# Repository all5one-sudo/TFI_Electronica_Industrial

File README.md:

# Electrónica Industrial: Trabajo Final de Integración

## Consigna

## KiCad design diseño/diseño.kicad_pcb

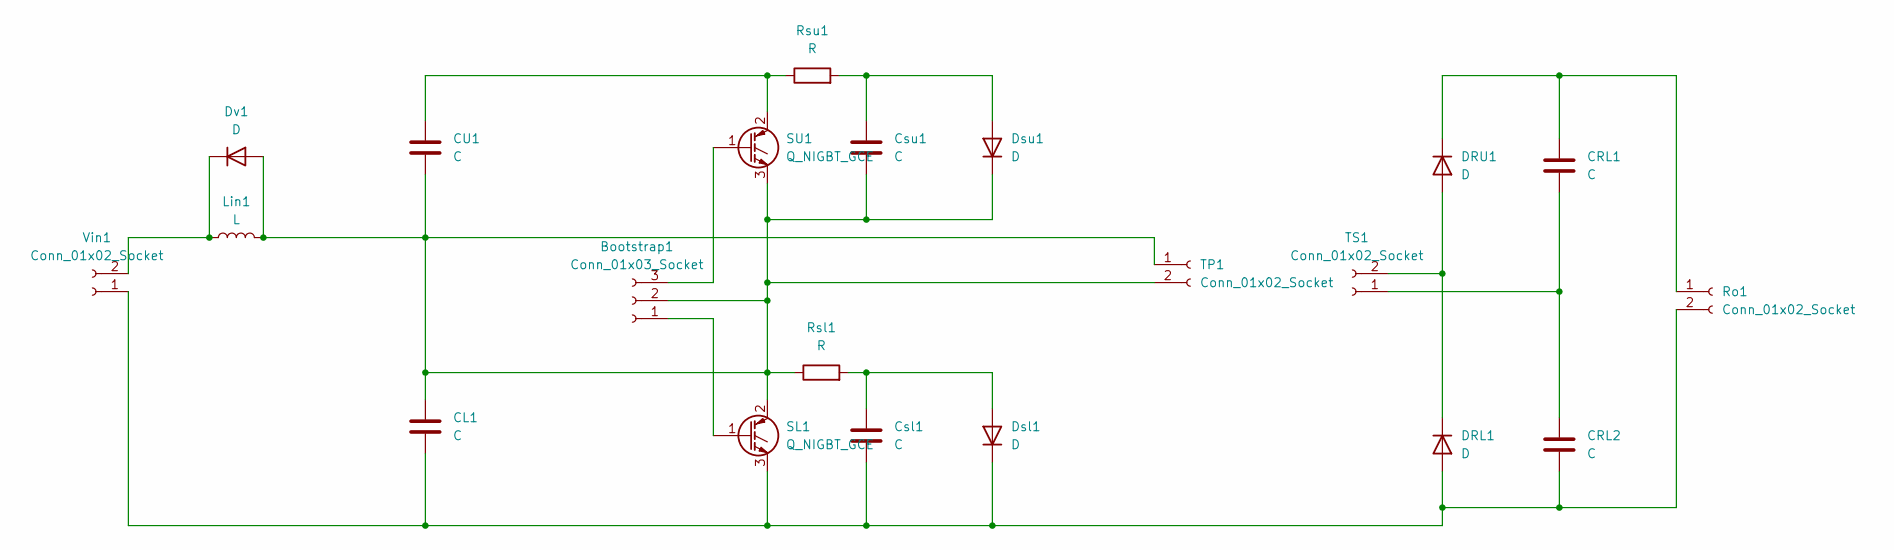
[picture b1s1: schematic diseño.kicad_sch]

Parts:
Bootstrap1: Conn_01x03_Socket; PinSocket_1x03_P2.54mm_Vertical
CL1: C; CP_Axial_L42.0mm_D35.0mm_P45.00mm_Horizontal
CRL1, CRL2: C; CP_Radial_D14.0mm_P7.50mm
CU1: C; CP_Axial_L42.0mm_D35.0mm_P45.00mm_Horizontal
Csl1: C; C_Rect_L13.0mm_W4.0mm_P10.00mm_FKS3_FKP3_MKS4
Csu1: C; C_Rect_L13.0mm_W4.0mm_P10.00mm_FKS3_FKP3_MKS4
DRL1: D; TO-220-2_Vertical
DRU1: D; TO-220-2_Vertical
Dsl1: D; D_DO-41_SOD81_P7.62mm_Horizontal
Dsu1: D; D_DO-41_SOD81_P7.62mm_Horizontal
Dv1: D; D_5KP_P10.16mm_Horizontal
Lin1: L; L_Axial_L30.0mm_D8.0mm_P7.62mm_Vertical_Fastron_77A
Ro1: Conn_01x02_Socket; PhoenixContact_MCV_1,5_2-G-5.08_1x02_P5.08mm_Vertical
Rsl1: R; R_Axial_DIN0918_L18.0mm_D9.0mm_P7.62mm_Vertical
Rsu1: R; R_Axial_DIN0918_L18.0mm_D9.0mm_P7.62mm_Vertical
SL1: Q_NIGBT_GCE; TO-264-3_Vertical
SU1: Q_NIGBT_GCE; TO-264-3_Vertical
TP1: Conn_01x02_Socket; PhoenixContact_MCV_1,5_2-G-5.08_1x02_P5.08mm_Vertical
TS1: Conn_01x02_Socket; PhoenixContact_MCV_1,5_2-G-5.08_1x02_P5.08mm_Vertical
Vin1: Conn_01x02_Socket; PhoenixContact_MCV_1,5_2-G-5.08_1x02_P5.08mm_Vertical

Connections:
unnamed: Bootstrap1.1, SL1.1 (G)
unnamed: Bootstrap1.2, CL1.1, CU1.2, Csu1.2, Dsu1.1 (K), Dv1.2 (A), Lin1.2, Rsl1.1, SL1.2 (C), SU1.3 (E), TP1.1, TP1.2
unnamed: Bootstrap1.3, SU1.1 (G)
unnamed: CL1.2, CRL2.2, Csl1.2, DRL1.2 (A), Dsl1.1 (K), Ro1.2, SL1.3 (E), Vin1.1
unnamed: DRL1.1 (K), DRU1.2 (A), TS1.2
unnamed: CRL1.1, DRU1.1 (K), Ro1.1
unnamed: Csl1.1, Dsl1.2 (A), Rsl1.2
unnamed: Csu1.1, Dsu1.2 (A), Rsu1.2
unnamed: Dv1.1 (K), Lin1.1, Vin1.2
unnamed: CU1.1, Rsu1.1, SU1.2 (C)
unnamed: CRL1.2, CRL2.1, TS1.1

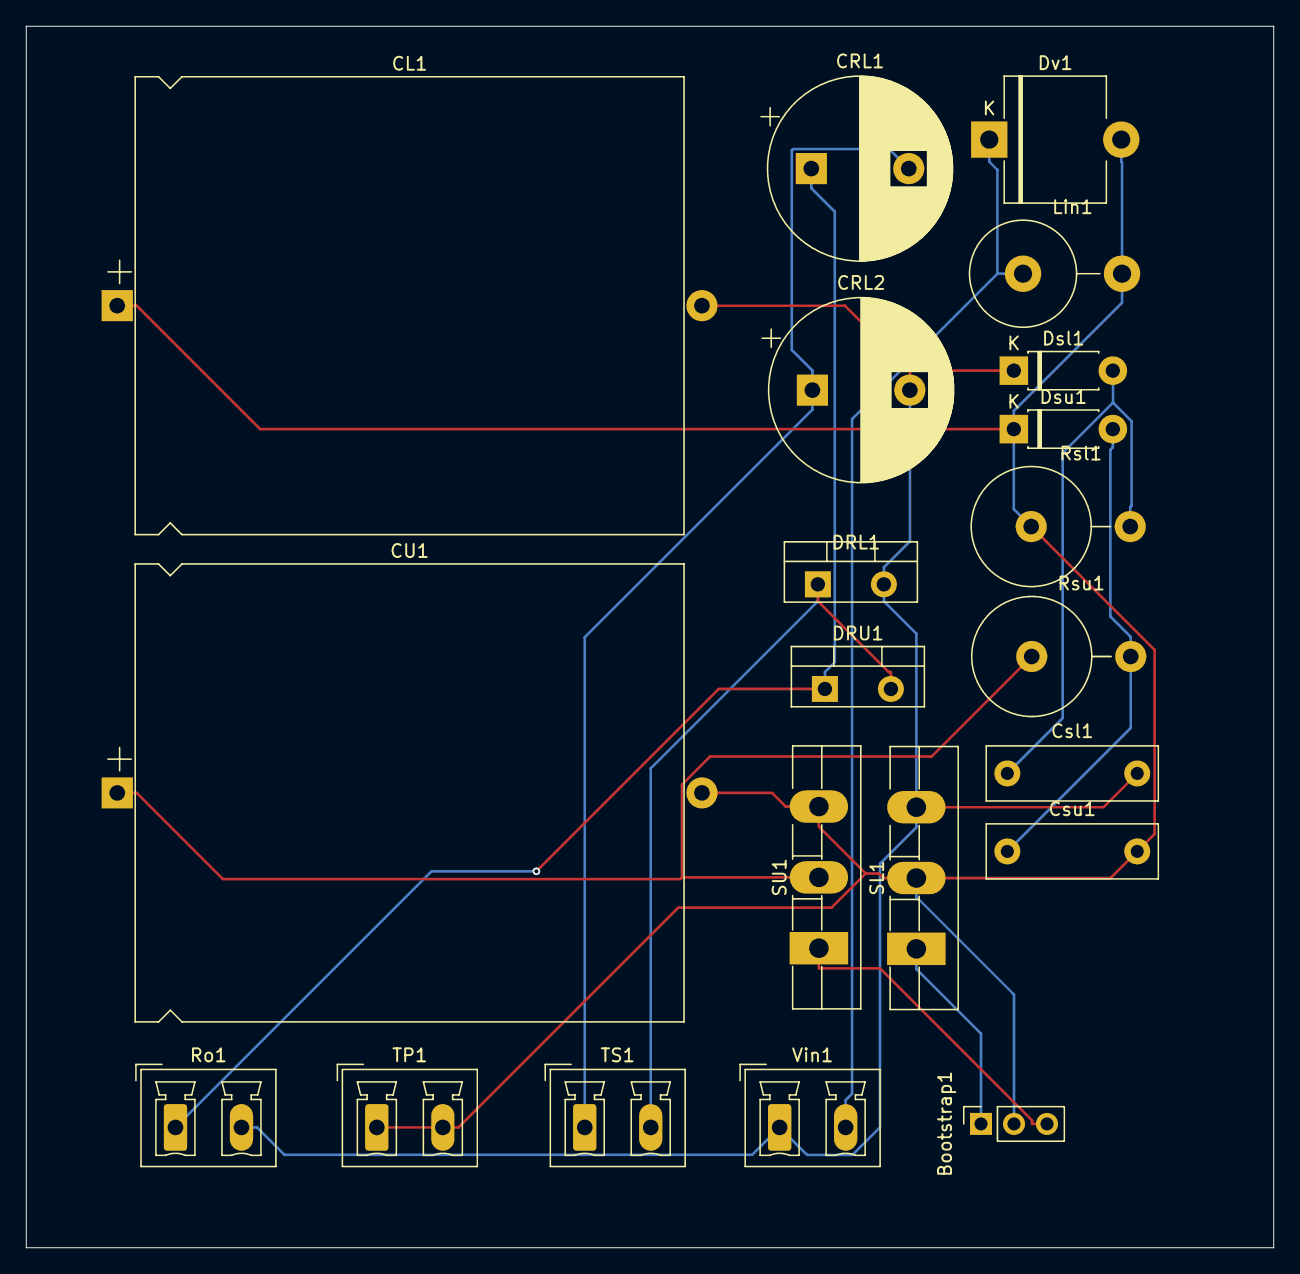
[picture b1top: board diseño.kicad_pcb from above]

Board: 2 copper layers, 96.0 x 94.0 mm, 21 parts (0 on the bottom side), 11 nets.

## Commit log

2024-06-02 Añadido consigna
2024-06-06 Actualización general
2024-06-08 Avances
2024-06-09 Simulacion funcionando
2024-06-10 Añadido simulación PLECS funcional y avances en el informe
2024-06-11 Modificación alimentación
2024-06-12 Simulacion funcionando con topología original
2024-06-12 Transitorios corregidos
2024-06-12 Reorganización y añadido simulación LTSpice
2024-06-13 Modificación alimentación a 48V
2024-06-13 Nueva simulación funcionando
    Ajustada nueva tensión de entrada y corriente de salida. Formas de onda correctas. Resta selección de componentes y completar informe.
2024-06-14 Avances en simulación e informe
2024-06-14 Diseño PCB
2024-06-17 Trabajo completo
